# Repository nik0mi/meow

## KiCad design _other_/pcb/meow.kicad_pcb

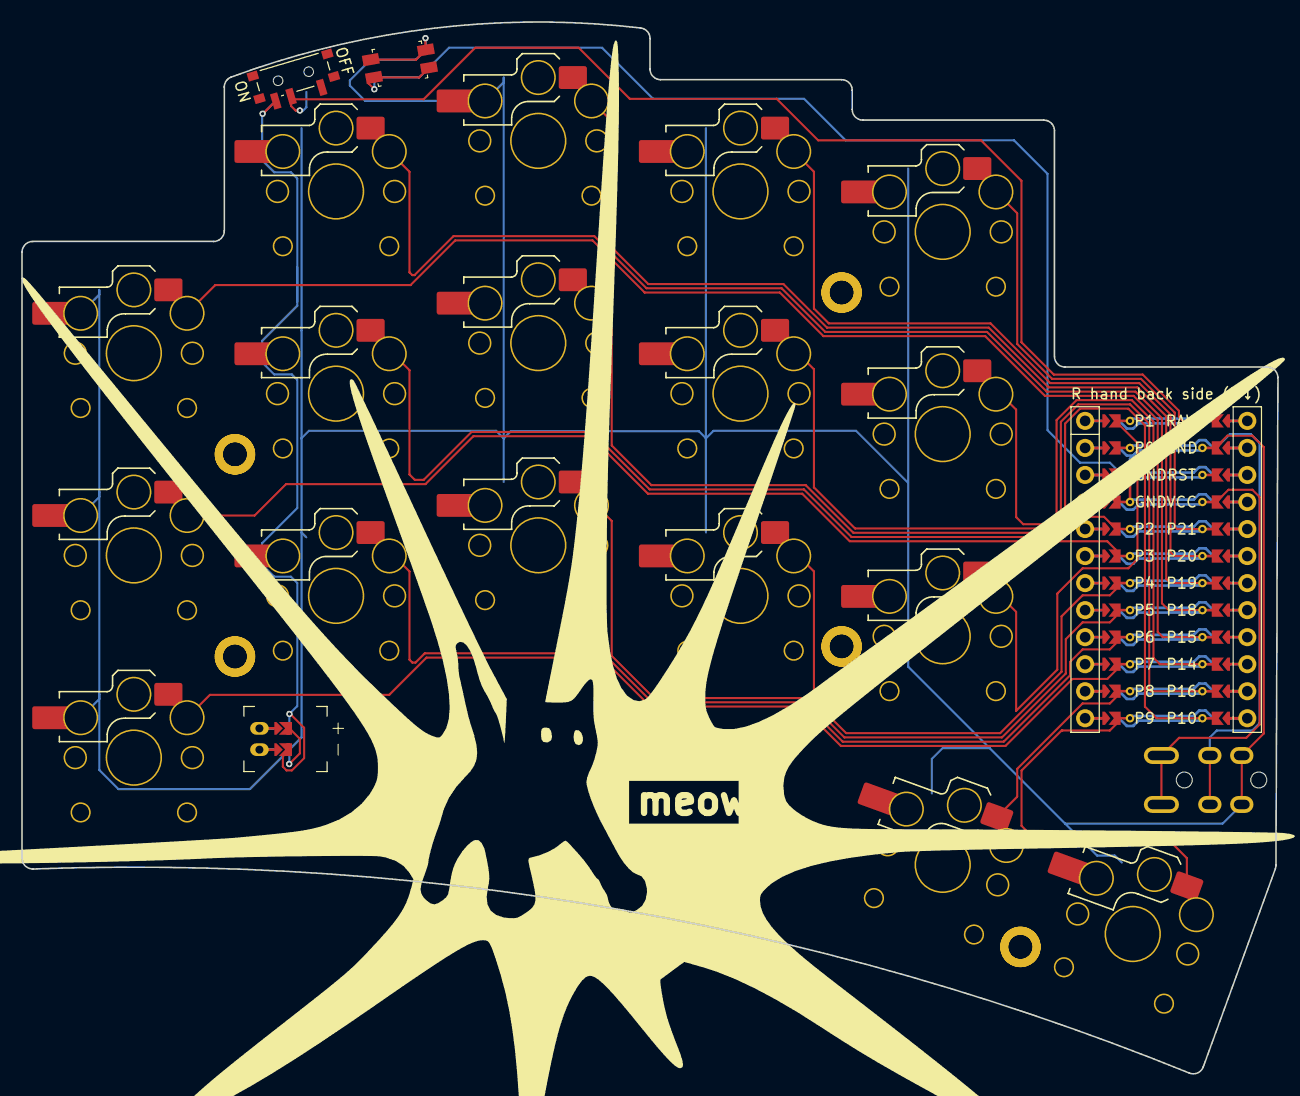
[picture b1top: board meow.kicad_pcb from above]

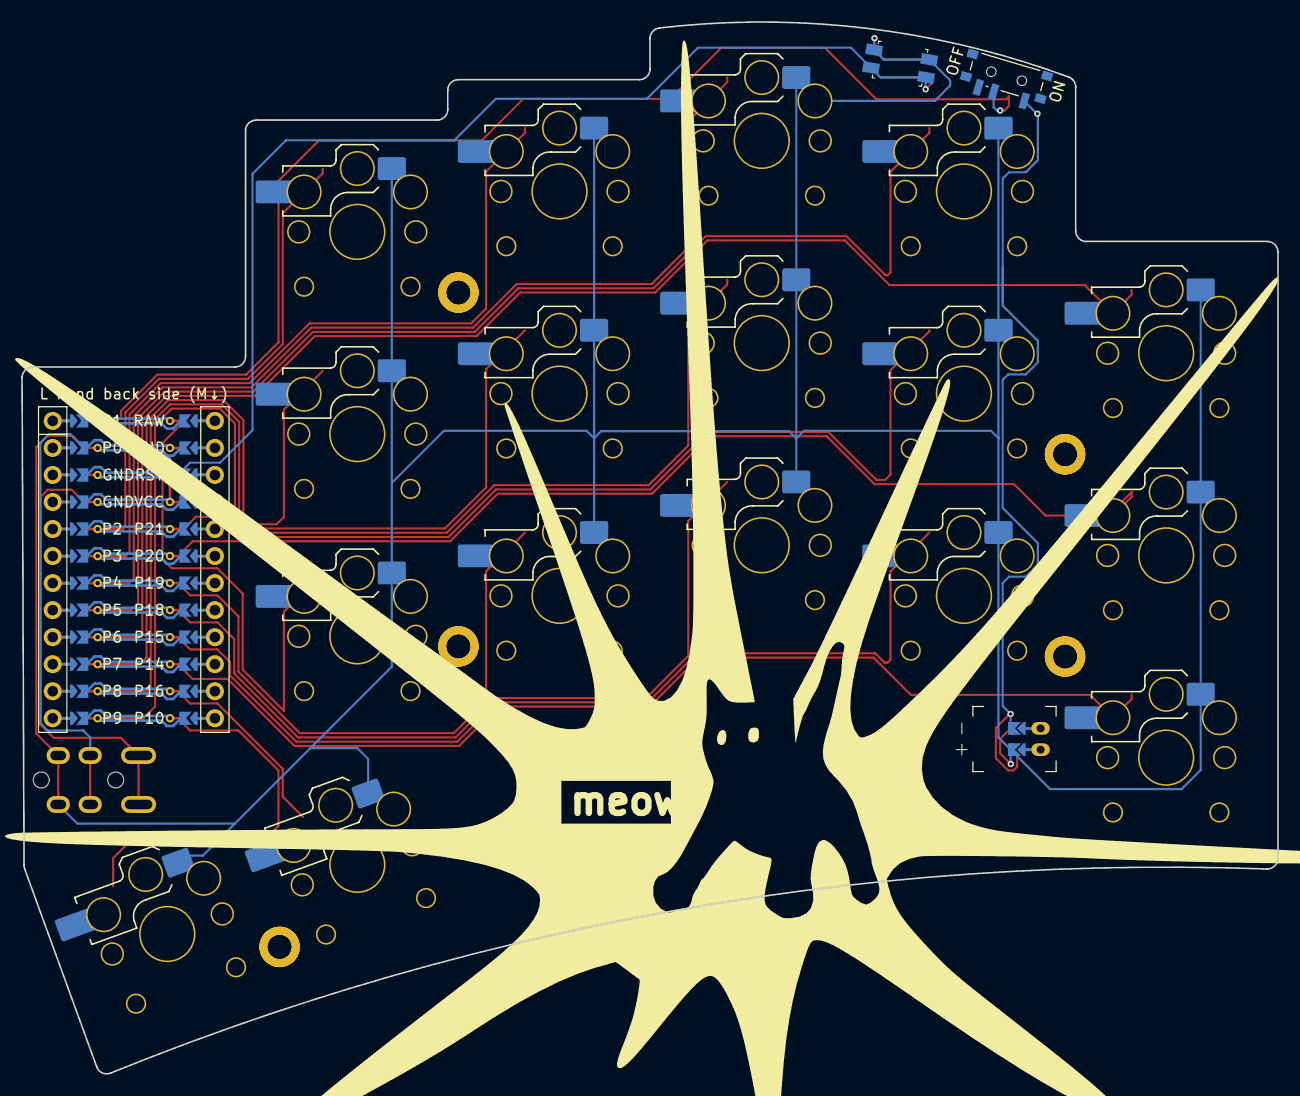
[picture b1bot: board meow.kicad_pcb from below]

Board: 2 copper layers, 118.0 x 98.8 mm, 32 parts (22 on the bottom side), 25 nets.

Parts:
H1, H2, H3, H4, H5, H6, H7, H8, H9, H10: mounting_hole_plated
JST1: battery_connector_jst_ph_2
MCU1: mcu_supermini_nrf52840
PWR1: power_switch_smd_side
RST1: reset_switch_smd_side
S1, S2, S3, S4, S5, S6, S7, S8, S9, S10, S11, S12, S13, S14, S15, S16, S17: switch_choc_v1_v2
TRRS1: trrs_pj320a (reversible, symmetric)

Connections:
BAT_P: JST1.1, PWR1.1, PWR1.3
GND: JST1.2, MCU1.102, MCU1.121, MCU1.122, RST1.1, RST1.3, S1.1, S2.1, S3.1, S4.1, S5.1, S6.1, S7.1, S8.1, S9.1, S10.1, S11.1, S12.1, S13.1, S14.1, S15.1, S16.1, S17.1, TRRS1.2
JST1_1: JST1.11, JST1.21, JST1.31
JST1_2: JST1.12, JST1.22, JST1.32
P0: MCU1.123, TRRS1.3
RAW: MCU1.101, PWR1.2
RST: MCU1.103, RST1.2, RST1.4
VCC: MCU1.104, TRRS1.4
matrix_index_bottom: MCU1.118, S10.2
matrix_index_home: MCU1.111, S11.2
matrix_index_top: MCU1.106, S12.2
matrix_inner_bottom: MCU1.124, S13.2
matrix_inner_home: MCU1.110, S14.2
matrix_inner_top: MCU1.105, S15.2
matrix_middle_bottom: MCU1.117, S7.2
matrix_middle_home: MCU1.112, S8.2
matrix_middle_top: MCU1.107, S9.2
matrix_pinky_bottom: MCU1.115, S1.2
matrix_pinky_home: MCU1.119, S2.2
matrix_pinky_top: MCU1.109, S3.2
matrix_ring_bottom: MCU1.116, S4.2
matrix_ring_home: MCU1.120, S5.2
matrix_ring_top: MCU1.108, S6.2
thumb_reachy: MCU1.113, S17.2
thumb_tucky: MCU1.114, S16.2

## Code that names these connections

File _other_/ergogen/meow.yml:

meta:
  engine: 4.1.0
units:
  kx: u
  ky: u
  px: kx + 2
  py: ky + 2
points:
  zones:
    matrix:
      anchor.shift: [50,-100]
      columns:
        pinky:
        ring.key.stagger: 0.8kx
        middle.key.stagger: 0.25kx
        index.key.stagger: -0.25kx
        inner.key.stagger: -0.2kx
      rows:
        bottom.padding: kx
        home.padding: kx
        top.padding: kx
    thumb:
      anchor:
        ref: matrix_index_bottom
        shift: [1kx, -1.33ky]
        rotate: -20
      columns:
        tucky.key.name: thumb_tucky
        reachy.key.name: thumb_reachy
outlines:
  keys:
    - what: rectangle
      where: true
      size: [18, 18]
  cutouts:
    - what: rectangle
      where: true
      size: [14,14]
  _mcu:
    - what: rectangle
      where:
        ref: matrix_inner_bottom
        shift: [py, 7.265]
      size: [17.78,33]
  _holes:
    - what: circle
      where:
        ref: matrix_pinky_top
        shift: [0.5kx, -0.5ky]
      radius: 2
    - what: circle
      where:
        ref: matrix_pinky_bottom
        shift: [0.5kx, 0.5ky]
      radius: 2
    - what: circle
      where:
        ref: matrix_index_top
        shift: [0.5kx, -0.5ky]
      radius: 2
    - what: circle
      where:
        ref: matrix_index_bottom
        shift: [0.5kx, -0.25ky]
      radius: 2
    - what: circle
      where:
        ref: thumb_tucky
        shift: [0.5kx, -0.25ky]
      radius: 2
  board:
    - what: path
      fillet: 1
      segments: 
        - type: line
          points:
          - ref: thumb_reachy
            shift: [0.5px,0.5py]
          - ref: matrix_inner_home
            shift: [1.5px,0.3py]
          - ref: matrix_inner_home
            shift: [0.5px,0.3py]
          - ref: matrix_inner_top
            shift: [0.5px,0.5py] 
          - ref: matrix_inner_top
            shift: [-0.5px+2,0.5py]
          - ref: matrix_index_top
            shift: [0.5px,0.5py]     
          - ref: matrix_index_top
            shift: [-0.5px+2,0.5py]
          - ref: matrix_middle_top
            shift: [0.5px,0.5py]   
        - type: arc
          points:
          - ref: matrix_middle_top
            shift: [-0.5px,0.5py]    
          - ref: matrix_ring_top
            shift: [-0.5px,0.5py]  
        - type: line
          points:
          - ref: matrix_pinky_top
            shift: [0.5px-2,0.5py] 
          - ref: matrix_pinky_top
            shift: [-0.5px,0.5py] 
          - ref: matrix_pinky_bottom
            shift: [-0.5px,-0.5py]
        - type: arc
          points:    
          - ref: matrix_pinky_bottom
            shift: [0.5px,-0.5py] 
          - ref: thumb_reachy
            shift: [0.5px,-0.5py]
          

  preview:
    - what: outline
      name: board
    - what: outline
      name: _mcu
      operation: subtract
    - what: outline
      name: keys
      operation: subtract
    - what: outline
      name: _holes
      operation: stack
    - what: outline
      name: cutouts
      operation: add
  
  _prnt:
    - what: outline
      name: board
    - what: outline
      name: cutouts
      operation: subtract
cases:
  prnt:
    - name: _prnt
      extrude: 1
pcbs:
  meow:
    outlines:
      main:
        outline: board
    template: kicad8 
    footprints:
      keys:
        what: ceoloide/switch_choc_v1_v2
        where: true
        params:
          from: GND
          to: "{{name}}"
          reversible: true
          include_keycap: true
          include_plated_holes: true
          include_corner_marks: true
          switch_3dmodel_filename: ${KICAD6_3DMODEL_DIR}/switch.step
          keycap_3dmodel_filename: ${KICAD6_3DMODEL_DIR}/keycap.step
          keycap_3dmodel_xyz_offset: [0,0,5]
          hotswap_3dmodel_filename: ${KICAD6_3DMODEL_DIR}/hotswap.step
          hotswap_3dmodel_xyz_offset: [0,-6,-3]
      connector:
        what: ceoloide/battery_connector_jst_ph_2
        where:
          ref: matrix_pinky_bottom
          shift: [11.8, 1.75]
          rotate: 90
        params:
          reversible: true
          battery_connector_3dmodel_xyz_offset: [-1,0,0]
          battery_connector_3dmodel_filename: ${KICAD6_3DMODEL_DIR}/jst-ph.step
      power_switch:
        what: ceoloide/power_switch_smd_side
        where:
          ref: matrix_ring_top
          shift: [-4,10.8]
          rotate: 106.5
        params:
          reversible: true
          invert_behavior: true
          switch_3dmodel_xyz_rotation: [0,0,90]
          switch_3dmodel_filename: ${KICAD6_3DMODEL_DIR}/power_switch.step
      reset_switch:
        what: ceoloide/reset_switch_smd_side
        where:
          ref: matrix_ring_top
          shift: [6, 12]
          rotate: 10
        params:
          reversible: true
          reset_switch_3dmodel_filename: ${KICAD6_3DMODEL_DIR}/reset_switch.step
      trrs:
        what: ceoloide/trrs_pj320a
        where:
          ref: matrix_inner_bottom
          shift: [31.3, -13.5]
          rotate: -90
        params:
          reversible: true
          symmetric: true
          TP: VCC
          R2: P0
          SL: GND
      mcu:
        what: ceoloide/mcu_supermini_nrf52840
        where:
          - ref: matrix_inner_bottom
            shift: [px, 7.54]
        params:
          reversible: true
          reverse_mount: true

          P21: matrix_inner_top
          P21_label: P21
          P20: matrix_index_top
          P20_label: P20
          P19: matrix_middle_top
          P19_label: P19
          P18: matrix_ring_top
          P18_label: P18
          P15: matrix_pinky_top
          P15_label: P15

          P14: matrix_inner_home
          P14_label: P14
          P16: matrix_index_home
          P16_label: P16
          P10: matrix_middle_home
          P10_label: P10
          P2: matrix_ring_home
          P2_label: P2
          P3: matrix_pinky_home
          P3_label: P3

          P1: matrix_inner_bottom
          P1_label: P1
          P4: matrix_index_bottom
          P4_label: P4
          P5: matrix_middle_bottom
          P5_label: P5
          P6: matrix_ring_bottom
          P6_label: P6
          P7: matrix_pinky_bottom
          P7_label: P7

          P8: thumb_tucky
          P8_label: P8
          P9: thumb_reachy
          P9_label: P9

      hole_1:
        what: ceoloide/mounting_hole_plated
        where:
          ref: matrix_pinky_top
          shift: [0.5kx , -0.5ky]
      hole_2:
        what: ceoloide/mounting_hole_plated
        where:
          ref: matrix_pinky_bottom
          shift: [0.5kx , 0.5ky]
      hole_3:
        what: ceoloide/mounting_hole_plated
        where:
          ref: matrix_index_top
          shift: [0.5kx , -0.5ky]
      hole_4:
        what: ceoloide/mounting_hole_plated
        where:
          ref: thumb_tucky
          shift: [0.5kx , -0.25ky]
      hole_5:
        what: ceoloide/mounting_hole_plated
        where:
          ref: matrix_index_bottom
          shift: [0.5kx , -0.25ky]
      hole_1B:
        what: ceoloide/mounting_hole_plated
        params.side: 'B'
        where:
          ref: matrix_pinky_top
          shift: [0.5kx , -0.5ky]
      hole_2B:
        what: ceoloide/mounting_hole_plated
        params.side: 'B'
        where:
          ref: matrix_pinky_bottom
          shift: [0.5kx , 0.5ky]
      hole_3B:
        what: ceoloide/mounting_hole_plated
        params.side: 'B'
        where:
          ref: matrix_index_top
          shift: [0.5kx , -0.5ky]
      hole_4B:
        what: ceoloide/mounting_hole_plated
        params.side: 'B'
        where:
          ref: thumb_tucky
          shift: [0.5kx , -0.25ky]
      hole_5B:
        what: ceoloide/mounting_hole_plated
        params.side: 'B'
        where:
          ref: matrix_index_bottom
          shift: [0.5kx , -0.25ky]
